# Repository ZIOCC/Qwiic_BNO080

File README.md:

# Zio Qwiic 9DOF IMU BNO080

> This product can be available for purchase [here](https://www.smart-prototyping.com/Zio-9DOF-IMU-BNO080.html).

#### Description

This IC has a combination triple axis accelerometer/gyro/magnetometer packaged with an ARM Cortex M0+ running powerful algorithms. The BNO080 Inertial Measurement Unit (IMU) produces accurate rotation vector headings, excellently suited for VR and other heading applications with a static rotation error of 2 degrees or less. It’s what we’ve been waiting for: all the sensor data is combined and drift corrected into meaningful, accurate IMU information.

> Note: As with all of the Version 1.0 Zio Qwiic boards, this board has been produced with the I2C pull-ups disconnected by default. If there's a significant length of wire between this board and your MCU, you'll need to solder closed the solder jumpers (labeled SDA, 3v3 and SCL) to connect the pull-up resistors to VCC.

#### Specification

* Rotation Vector
  * Dynamic Error: 3.5°
  * Static Error: 2.0°
* Gaming Rotation Vector
  * Dynamic Error: 2.5°
  * Static Error: 1.5°
  * Heading Drift: 0.5° / min
* Geomagnetic Rotation Vector
  * Dynamic Rotation Error: 4.5°
  * Static Rotation Error: 3.0°
* Gravity Angle Error: 1.5°
* Linear Acceleration Accuracy: 0.35m/s2
* Accelerometer Accuracy: 0.3m/s2
* Gyroscope Accuracy: 3.1° / sec
* Magnetometer Accuracy: 1.4µT
* IC: BNO080
* I2C address: 0x4A, 0x4B (Default: 0x4A)
* Dimension: 13.9x 36.2mm(with mounting tab), 13.9x24.7mm(without mounting tab).
* Weight: 1.2g

#### Links

* [Eagle File and Schematic](https://github.com/ZIOCC/Qwiic_BNO080)
* [BNO080 Datasheet](https://www.smart-prototyping.com/image/data/NOA-RnD/101894%209DOF%20IMU%20BNO080/BNO080%20Datasheet%20v1.3.pdf)
* [SparkFun Library](https://github.com/sparkfun/SparkFun_BNO080_Arduino_Library)

> ###### About Zio
> Zio is a new line of open sourced, compact, and grid layout boards, fully integrated for Arduino and Qwiic ecosystem. Designed ideally for wearables, robotics, small-space limitations or other on the go projects. Check out other awesome Zio products [here](https://www.smart-prototyping.com/Zio).

> All Zio products are released under the [Creative Commons Attribution, Share-Alike License](https://creativecommons.org/licenses/by-sa/4.0/), and in accordance with the principles of the [Open Source Hardware Association's OSHW Statement of Principles 1.0 and OSHW Definition 1.0](https://www.oshwa.org/definition/).

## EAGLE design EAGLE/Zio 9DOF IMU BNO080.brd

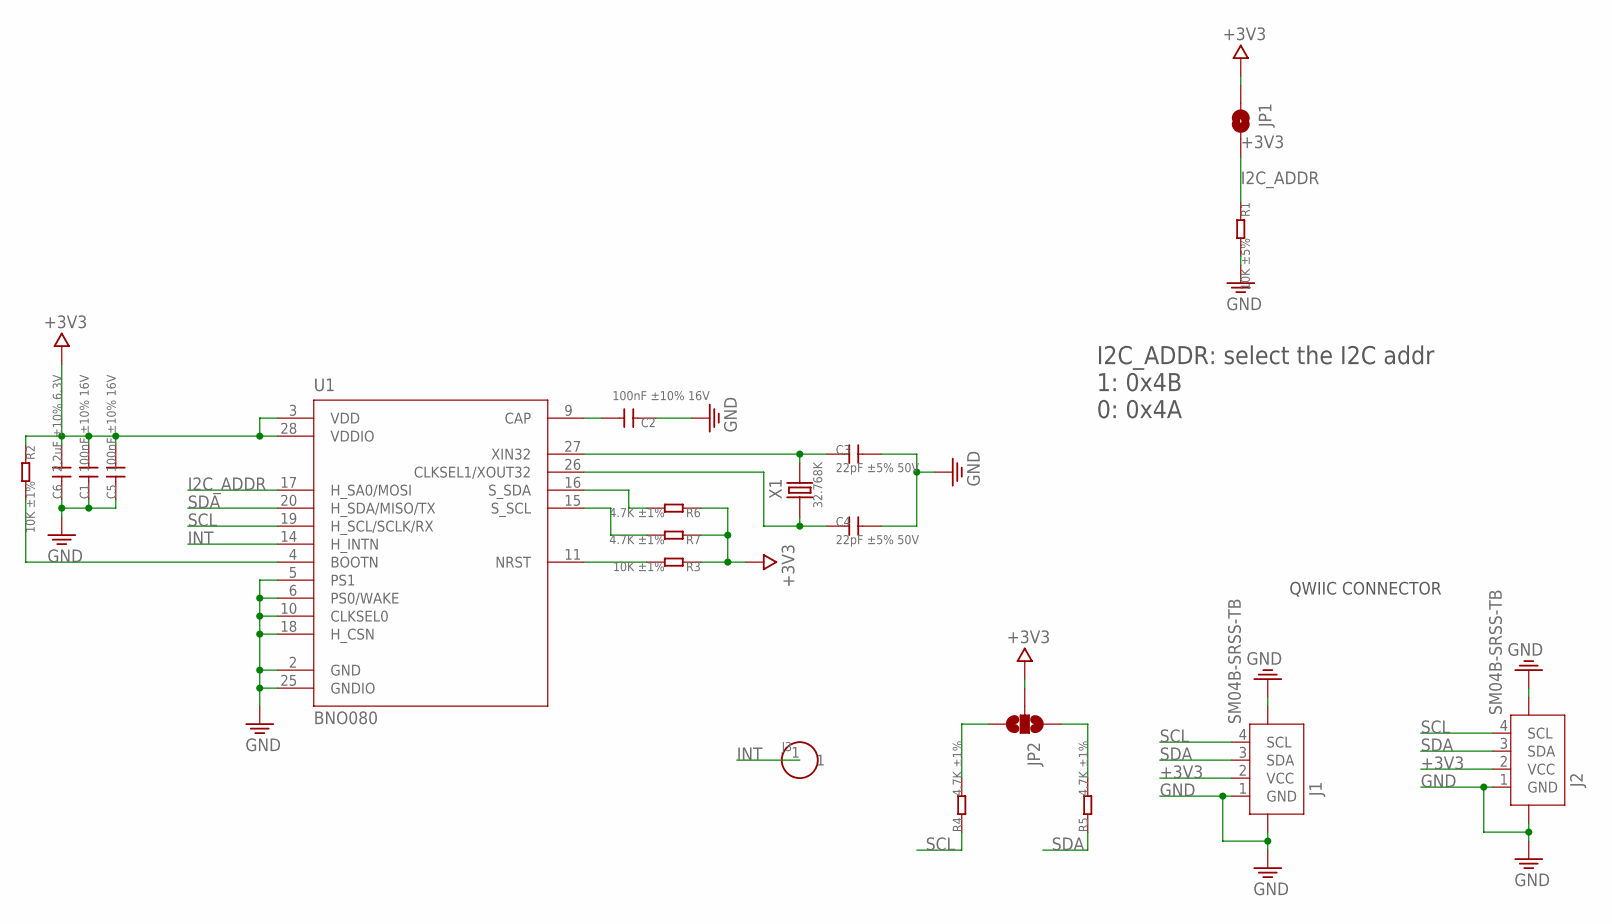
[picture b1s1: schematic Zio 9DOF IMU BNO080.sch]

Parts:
C1, C2, C5: 100nF ±10% 16V; 0402
C3, C4: 22pF ±5% 50V; 0402
C6: 2.2uF ±10% 6.3V; 0402
J1, J2: SM04B-SRSS-TB; JST-SH-4P
J3: HEADER-1P-40MIL; 1P-40MIL-AUTO
JP1: JUMPER-SMT_2_NO_SILK; SMT-JUMPER_2_NO_SILK
JP2: JUMPER-SMT_3_2-NC_PASTE_NOCREM; SMT-JUMPER_3_2-NC_PASTE_SILK_NOCREM
R1: 10K ±5%; 0402
R2, R3: 10K ±1%; 0402
R4, R5, R6, R7: 4.7K ±1%; 0402
U1: BNO080; IC_LGA-28_3.80X5.20/0.5
X1: 32.768K; 2.0X12MM

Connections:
+3V3: C1.2, C5.2, C6.2, J1.2 (VCC), J2.2 (VCC), JP1.1, JP2.2, R2.1, R3.1, R6.1, R7.1, U1.3 (VDD), U1.28 (VDDIO)
GND: C1.1, C2.1, C3.2, C4.2, C5.1, C6.1, J1.1 (GND), J1.NC1 (5), J1.NC2 (6), J2.1 (GND), J2.NC1 (5), J2.NC2 (6), R1.2, U1.2 (GND), U1.5 (PS1), U1.6 (PS0/WAKE), U1.10 (CLKSEL0), U1.18 (H_CSN), U1.25 (GNDIO)
I2C_ADDR: JP1.2, R1.1, U1.17 (H_SA0/MOSI)
INT: J3.1, U1.14 (H_INTN)
unnamed: C2.2, U1.9 (CAP)
unnamed: R3.2, U1.11 (NRST)
unnamed: R6.2, U1.16 (S_SDA)
unnamed: C3.1, U1.27 (XIN32), X1.2
unnamed: C4.1, U1.26 (CLKSEL1/XOUT32), X1.1
unnamed: R2.2, U1.4 (BOOTN)
unnamed: R7.2, U1.15 (S_SCL)
unnamed: JP2.3, R4.2
unnamed: JP2.1, R5.2
SCL: J1.4 (SCL), J2.4 (SCL), R4.1, U1.19 (H_SCL/SCLK/RX)
SDA: J1.3 (SDA), J2.3 (SDA), R5.1, U1.20 (H_SDA/MISO/TX)

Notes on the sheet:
I2C_ADDR: select the I2C addr 1: 0x4B 0: 0x4A
QWIIC CONNECTOR

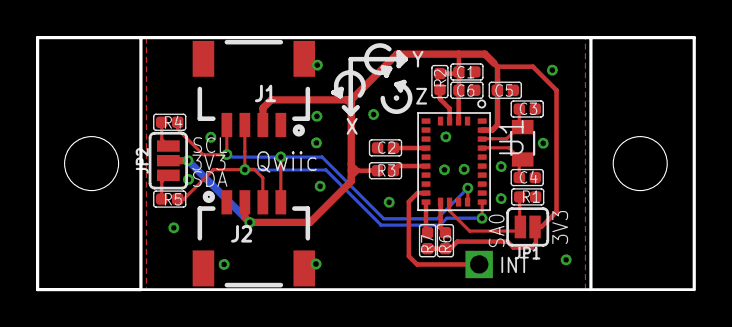
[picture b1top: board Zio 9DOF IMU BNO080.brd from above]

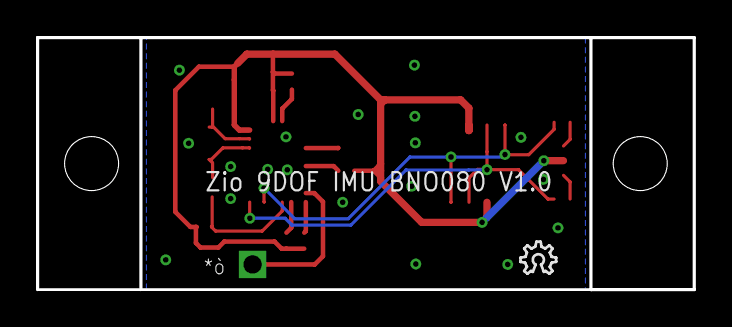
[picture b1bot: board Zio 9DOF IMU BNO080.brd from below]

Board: 2 copper layers, 36.5 x 14.0 mm, 23 parts (2 on the bottom side), 15 nets.

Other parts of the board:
E$3: 6MM
LOGO2: LOGO-OSHW-6MILX0070-NT; OSHW_6X70_NOTEXT
U$6: 6MM

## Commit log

2018-07-09 Eagle PCB schematic and layout initial upload
2018-08-07 Add files via upload
    PDF version of ZIO Qwiic BNO080 schematic

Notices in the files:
parts and their libraries:
SparkFun-Jumpers: Licensing: Creative Commons ShareAlike 4.0 International - https://creativecommons.org/licenses/by-sa/4.0
